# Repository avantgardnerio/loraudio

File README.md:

# open-oswst

Stealth LoRa radio mesh where the primary design principle is "only speak when spoken to".

## Hardware

- **Board**: [Heltec WiFi LoRa 32 V4](https://heltec.org/project/wifi-lora-32-v4/) (ESP32-S3 + SX1262, 863-928 MHz)
- **MCU**: ESP32-S3 rev 0.2, 16MB flash, 338 KiB RAM
- **Radio**: Semtech SX1262 LoRa transceiver, 915 MHz ISM band
- **Display**: SSD1306 128x64 OLED (I2C)

### Pin Map

| Function | GPIO |
|---|---|
| PRG button (PTT) | 0 (active LOW, internal pull-up) |
| White LED | 35 |
| Vext power enable | 36 (LOW = on) |
| OLED SDA | 17 |
| OLED SCL | 18 |
| OLED RST | 21 |
| LoRa SCK | 9 |
| LoRa MOSI | 10 |
| LoRa MISO | 11 |
| LoRa NSS | 8 |
| LoRa RST | 12 |
| LoRa DIO1 | 14 |
| LoRa BUSY | 13 |

## Dev Environment Setup

### Prerequisites

1. **Install Rust + Xtensa toolchain** via [espup](https://github.com/esp-rs/espup):

```bash
cargo install espup
espup install
```

2. **Create an ESP environment export script** (`~/export-esp.sh`):

```bash
export LIBCLANG_PATH="$HOME/.rustup/toolchains/esp/xtensa-esp32-elf-clang/esp-20.1.1_20250829/esp-clang/lib"
export PATH="$HOME/.rustup/toolchains/esp/xtensa-esp-elf/esp-15.2.0_20250920/xtensa-esp-elf/bin:$PATH"
```

The exact paths may vary — check `~/.rustup/toolchains/esp/` after `espup install`.

3. **Install flashing tools**:

```bash
cargo install espflash cargo-espflash ldproxy
```

4. **Optional**: install `picocom` for serial monitoring:

```bash
sudo apt install picocom
```

### Build

```bash
. ~/export-esp.sh
cargo build
```

ESP-IDF v5.5.x is downloaded automatically by `esp-idf-sys` on first build (takes a while).

### Flash

The firmware uses a custom partition table with a dedicated `open-oswst` NVS partition for device config. Since `espflash flash` overwrites the partition table with its own, you must re-write ours after flashing:

```bash
. ~/export-esp.sh

# 1. Flash firmware
espflash flash -p /dev/ttyACM0 target/xtensa-esp32s3-espidf/debug/open-oswst

# 2. Overwrite partition table with ours (espflash clobbers it in step 1)
espflash write-bin -p /dev/ttyACM0 0x8000 target/xtensa-esp32s3-espidf/debug/partition-table.bin

# 3. Write device config (only needed on first flash or to change config)
espflash write-bin -p /dev/ttyACM0 0xfad000 ~/phy/open-oswst_nvs.bin
```

Monitor separately:

```bash
picocom /dev/ttyACM0 -b 115200
```

### Device Config (NVS)

Device configuration lives in a dedicated `open-oswst` NVS partition at `0xfad000` (12KB), separate from the system NVS (PHY cal, WiFi, etc).

Generate a config image from `nvs_open-oswst.csv`:

```bash
# Generate NVS image (edit nvs_open-oswst.csv to change values)
python3 .embuild/espressif/python_env/idf5.5_py3.13_env/lib/python3.13/site-packages/esp_idf_nvs_partition_gen/nvs_partition_gen.py \
    generate nvs_open-oswst.csv ~/phy/open-oswst_nvs.bin 0x3000

# Flash to board
espflash write-bin -p /dev/ttyACM0 0xfad000 ~/phy/open-oswst_nvs.bin
```

Current config keys (namespace `config`):

| Key | Type | Values | Default |
|-----|------|--------|---------|
| `repeater` | u8 | 0=endpoint, 1=repeater | 0 |

There is also `nvs_config.py` for read-modify-write of the *system* NVS partition (preserving PHY cal data etc), but the dedicated partition approach above is preferred.

## Current Behavior

- Simplex push-to-talk voice radio over LoRa
- Hold **PRG button** (GPIO 0) to talk — audio is captured, Codec2-encoded at 1200 bps, and streamed as 4-frame LoRa packets (160ms audio each)
- Release to listen — received audio is decoded and played through I2S speaker (MAX98357A)
- OLED shows mode (RX Listening / TX Streaming / RX Audio) with RSSI and SNR on receive
- CSMA with preamble-aware jitter for collision avoidance
- Per-device config via dedicated NVS partition (repeater mode flag)
- **Next up**: repeater mesh relay

## Key Implementation Notes

- **Framework**: esp-idf-svc 0.52.1 (std Rust, not bare-metal)
- **Async**: `block_on` + `embassy_futures::select` for zero-polling PTT/RX racing
- **LoRa driver**: `lora-phy` (upstream git, 3.0.2-alpha) with `GenericSx126xInterfaceVariant`
- **GPIO type erasure**: `degrade_input()`/`degrade_output()` required for lora-phy's generic interface
- **SPI async**: `CONFIG_SPI_MASTER_ISR_IN_IRAM` disabled in `sdkconfig.defaults`
- **defmt workaround**: `defmt-discard.x` linker script discards defmt sections that break ESP-IDF flash layout
- **Stack**: 65536 bytes for main task (Codec2 init needs large stack temporaries)

## Project Structure

```
src/main.rs          # Entry point, channels, NVS config read
src/radio.rs         # SPI + LoRa init, IRQ-driven RX/TX loop, CSMA
src/app.rs           # PTT, ADC, OLED, Codec2, I2S speaker
partitions.csv       # Custom partition table (adds open-oswst NVS)
nvs_open-oswst.csv     # Default device config values
nvs_config.py        # Tool for read-modify-write of system NVS
sdkconfig.defaults   # ESP-IDF config overrides
defmt-discard.x      # Linker script to discard defmt sections
rust-toolchain.toml  # Pins to "esp" toolchain channel
build.rs             # Links defmt-discard.x
```

## Bill of Materials

### Handset (~$122)

| Component                                                                                       | Part                                                       | Qty | Est. Cost |
|-------------------------------------------------------------------------------------------------|------------------------------------------------------------|-----|-----------|
| [MCU + LoRa + GPS](https://www.amazon.com/dp/B0GCD9W6JZ?ref=ppx_yo2ov_dt_b_fed_asin_title&th=1) | Heltec WiFi LoRa 32 V4                                     | 1   | $42       |
| [RF amplifier](https://www.amazon.com/dp/B0DQBJVR91?ref=ppx_yo2ov_dt_b_fed_asin_title)          | AB-IOT-868 "Air Buddy" (902-928 MHz, bidirectional TX+LNA) | 1   | $26       |
| [Speaker amp](https://www.amazon.com/dp/B0DPJRLMDJ?ref=ppx_yo2ov_dt_b_fed_asin_title)           | MAX98357A I2S Class D breakout                             | 1   | $3        |
| [Speaker](https://www.amazon.com/dp/B0BTP67F81?ref=ppx_yo2ov_dt_b_fed_asin_title&th=1)          | 8 ohm 1W mini (JST-PH1.25mm)                               | 1   | $2.50     |
| [Microphone](https://www.amazon.com/dp/B0B7SP6GYX?ref=ppx_yo2ov_dt_b_fed_asin_title)            | MAX9814 electret with AGC (analog out)                     | 1   | $4        |
| [Antenna](https://www.amazon.com/dp/B0D47HVCK7?ref=ppx_yo2ov_dt_b_fed_asin_title&th=1)          | 5 dBi SMA whip (915 MHz)                                   | 1   | $6        |
| [Battery](https://www.amazon.com/dp/B0FPCWFFYB?ref=ppx_yo2ov_dt_b_fed_asin_title)               | YELUFT 1S 103450 3.7V 2000mAh LiPo (JST 1.25)              | 1   | $24       |
| [encoder](https://www.amazon.com/dp/B07F24TRYG?ref=ppx_yo2ov_dt_b_fed_asin_title)               | EC11 rotary encoder w/ push button (Taiss)                 | 2   | $1.25     |
| [Power switch](https://www.amazon.com/dp/B0DN69L9SG?ref=ppx_yo2ov_dt_b_fed_asin_title&th=1)     | SS12F15 mini slide switch (SPDT)                           | 1   | $0.30     |
| [PTT button](https://www.amazon.com/dp/B015X34IP6?ref=ppx_yo2ov_dt_b_fed_asin_title&th=1)       | Ulincos U16A1 16mm metal momentary, flush                  | 1   | $8        |
| [Speaker jack](https://www.amazon.com/dp/B01ASF0LW8?ref=ppx_yo2ov_dt_b_fed_asin_title)          | 2.5mm TRS chassis mount (Calrad 30-714 or similar)         | 1   | $0.66     |
| [Mic/PTT jack](https://www.amazon.com/dp/B00ZYWJ1DG?ref=ppx_yo2ov_dt_b_fed_asin_title)          | 3.5mm TRS chassis mount w/ switch (CESS)                   | 1   | $2        |
| [F2F SMA](https://www.amazon.com/dp/B0FB3R5WRL?ref=ppx_yo2ov_dt_b_fed_asin_title&th=1)          | Female to Female SMA                                       | 1 | $1        |

## License

TBD

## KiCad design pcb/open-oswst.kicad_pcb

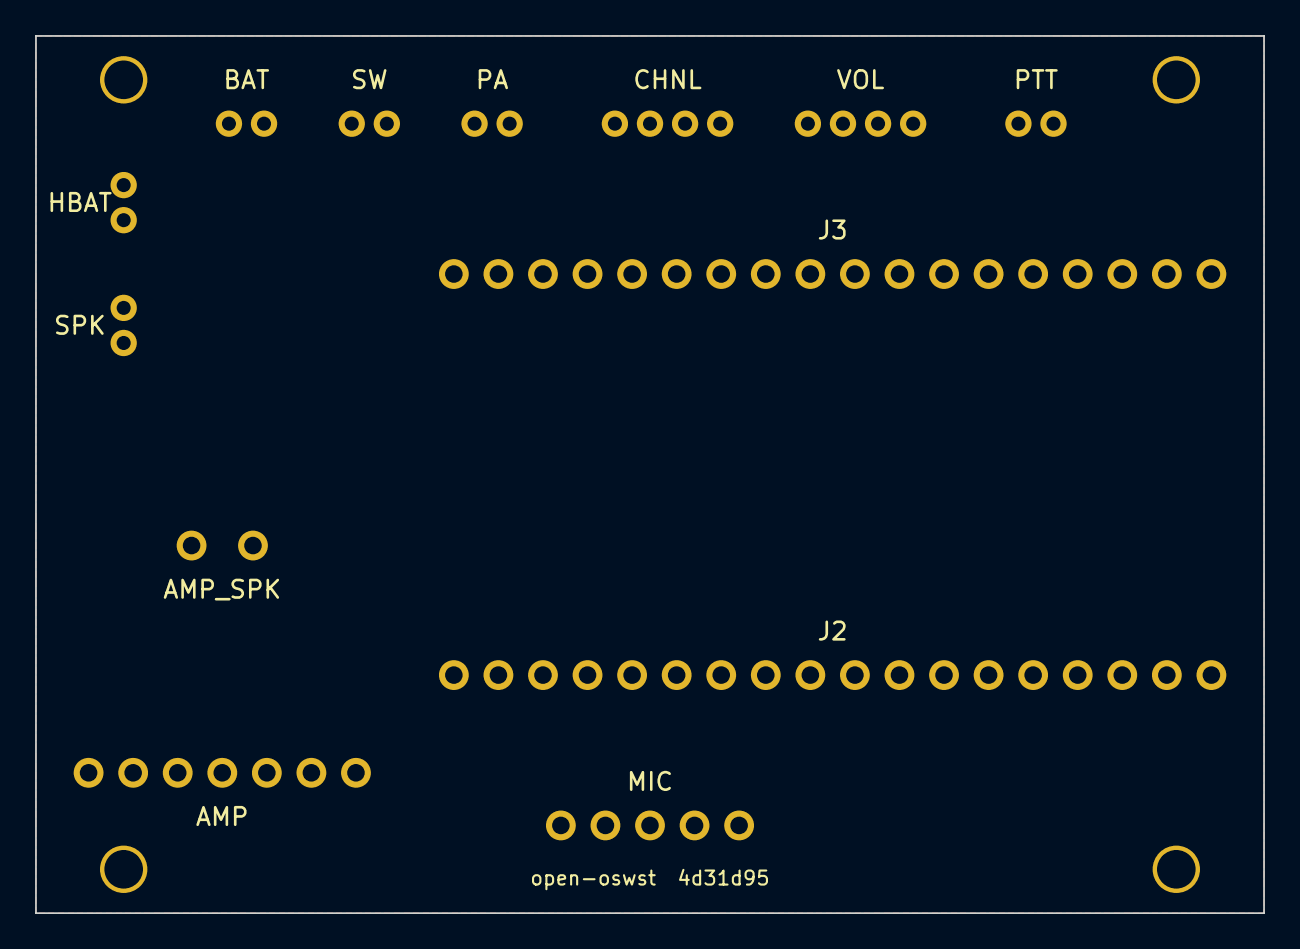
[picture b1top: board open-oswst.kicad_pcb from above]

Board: 2 copper layers, 70.0 x 50.0 mm, 17 parts (0 on the bottom side), 17 nets, no tracks yet.

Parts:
AMP: PinHeader_1x7_P2.54mm
AMP_SPK: PinHeader_1x2_P3.5mm
BAT: JST_PH_B2B
CHNL: JST_PH_B4B
H1, H2, H3, H4: MountingHole_2.2mm
HBAT: JST_PH_B2B
J2, J3: PinHeader_1x18_P2.54mm
MIC: PinHeader_1x5_P2.54mm
PA: JST_PH_B2B
PTT: JST_PH_B2B
SPK: JST_PH_B2B
SW: JST_PH_B2B
VOL: JST_PH_B4B

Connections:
BCLK: AMP.BCLK, J2.GPIO47
CHNL_A: CHNL.A, J3.GPIO7
CHNL_B: CHNL.B, J3.GPIO6
CHNL_SW: CHNL.SW, J3.GPIO5
DIN: AMP.DIN, J2.GPIO33
GND: AMP.GND, BAT.-, CHNL.GND, HBAT.-, J2.GND, J3.GND, MIC.GND, PA.-, PTT.2, VOL.GND
LRC: AMP.LRC, J2.GPIO48
MIC_OUT: J3.GPIO4, MIC.OUT
PTT: J2.GPIO0, PTT.1
SPK+: AMP_SPK.+, SPK.+
SPK-: AMP_SPK.-, SPK.-
VBAT: BAT.+, SW.1
VOL_A: J3.GPIO3, VOL.A
VOL_B: J3.GPIO2, VOL.B
VOL_SW: J3.GPIO1, VOL.SW
VSW: HBAT.+, PA.+, SW.2
Ve: AMP.Vin, J2.Ve_a, J2.Ve_b, MIC.VDD

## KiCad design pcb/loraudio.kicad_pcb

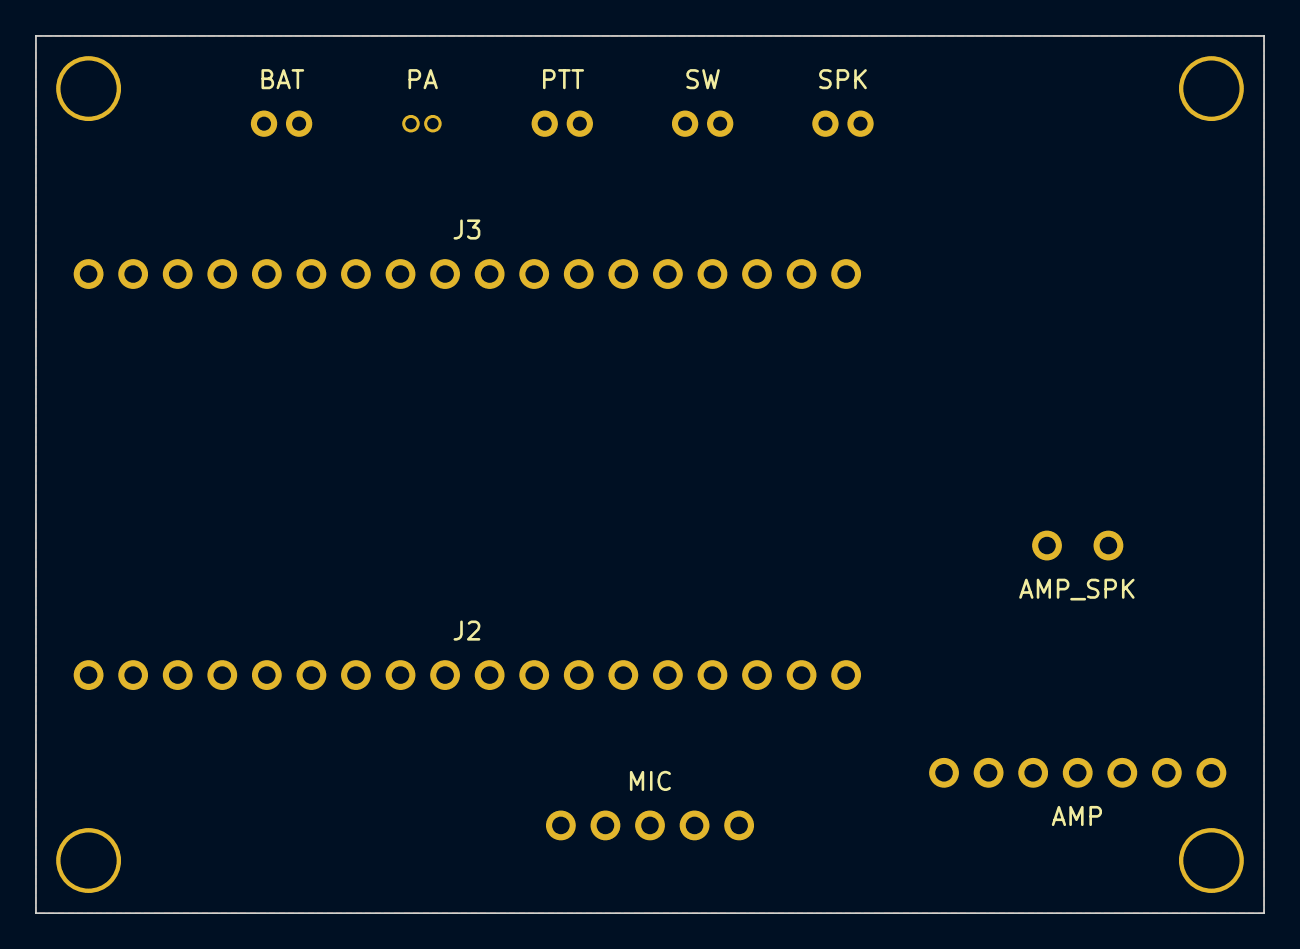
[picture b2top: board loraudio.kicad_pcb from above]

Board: 2 copper layers, 70.0 x 50.0 mm, 14 parts (0 on the bottom side), 11 nets, no tracks yet.

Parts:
AMP: PinHeader_1x7_P2.54mm
AMP_SPK: PinHeader_1x2_P3.5mm
BAT: JST_PH_B2B
H1, H2, H3, H4: MountingHole_3.2mm
J2, J3: PinHeader_1x18_P2.54mm
MIC: PinHeader_1x5_P2.54mm
PA: JST_SH_B2B
PTT: JST_PH_B2B
SPK: JST_PH_B2B
SW: JST_PH_B2B

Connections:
3V3: AMP.Vin, J3.3V3a, MIC.VDD
BCLK: AMP.BCLK, J3.GPIO3
DIN: AMP.DIN, J3.GPIO5
GND: AMP.GND, BAT.-, J2.GND, J3.GND, MIC.GND, PA.-, PTT.2
LRC: AMP.LRC, J3.GPIO4
MIC_OUT: J3.GPIO7, MIC.OUT
PTT: J2.GPIO0, PTT.1
SPK+: AMP_SPK.+, SPK.+
SPK-: AMP_SPK.-, SPK.-
VBAT: BAT.+, SW.1
VSW: J3.3V3b, PA.+, SW.2

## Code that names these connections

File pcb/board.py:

#!/usr/bin/env python3
"""Generate the open-oswst PCB."""

import subprocess
from kicad import Board

board = Board()
git_sha = subprocess.check_output(["git", "rev-parse", "--short", "HEAD"], text=True).strip()

# 70x50mm landscape, centered on A4 (297x210mm)
BX, BY = 113, 113  # board origin
BW, BH = 70, 50    # board size
INSET_LR = 5        # hole center distance from left/right edges
INSET_TB = 2.5      # hole center distance from top/bottom edges

board.add_rect(BX, BY, BW, BH)

for x in (BX + INSET_LR, BX + BW - INSET_LR):
    for y in (BY + INSET_TB, BY + BH - INSET_TB):
        board.add_mounting_hole(x, y, drill=2.2)

# Connectors along top edge — fit between drill holes (INSET_LR)
cx, cy = BX + INSET_LR + 7, BY + 5
board.add_jst_ph(cx, cy, pins=2, label="BAT",
                 pad_labels=["+", "-"], pad_nets=["VBAT", "GND"]); cx += 7
board.add_jst_ph(cx, cy, pins=2, label="SW",
                 pad_nets=["VBAT", "VSW"]); cx += 7
board.add_jst_ph(cx, cy, pins=2, label="PA",
                 pad_labels=["+", "-"], pad_nets=["VSW", "GND"]); cx += 10
board.add_jst_ph(cx, cy, pins=4, label="CHNL",
                 pad_labels=["A", "B", "SW", "GND"],
                 pad_nets=["CHNL_A", "CHNL_B", "CHNL_SW", "GND"]); cx += 11
board.add_jst_ph(cx, cy, pins=4, label="VOL",
                 pad_labels=["A", "B", "SW", "GND"],
                 pad_nets=["VOL_A", "VOL_B", "VOL_SW", "GND"]); cx += 10
board.add_jst_ph(cx, cy, pins=2, label="PTT",
                 pad_nets=["PTT", "GND"])

# HBAT: feeds VSW out to Heltec's onboard SH1.25-2P LiPo input via an M2M pigtail.
# Heltec's battery input accepts 3.3-4.2V (per datasheet 3.2), so raw LiPo is correct here.
# Placed above SPK so VSW from BAT/SW (top of board) doesn't cross the SPK+/SPK- traces.
board.add_jst_ph(BX + 5, BY + INSET_TB + 7, pins=2, label="HBAT", angle=90,
                 pad_labels=["+", "-"], pad_nets=["VSW", "GND"])

# SPK connector on left edge (rotated 90°, routes down to AMP_SPK)
board.add_jst_ph(BX + 5, BY + INSET_TB + 14, pins=2, label="SPK", angle=90,
                 pad_labels=["-", "+"], pad_nets=["SPK-", "SPK+"])

# Heltec V4 headers — two 18-pin rows
J3_SPAN = 17 * 2.54  # 18 pins, 17 gaps
HELTEC_WIDTH = 22.86  # distance between J3 and J2 header rows
HY = BY + BH / 2 - HELTEC_WIDTH / 2  # J3 y (top row)

board.add_header(BX + BW - 3 - J3_SPAN / 2, HY, pins=18, label="J3",
                 pad_labels=["GPIO7", "GPIO6", "GPIO5", "GPIO4", "GPIO3", "GPIO2",
                             "GPIO1", "GPIO38", "GPIO39", "GPIO40", "GPIO41", "GPIO42",
                             "GPIO45", "GPIO46", "GPIO37", "3V3a", "3V3b", "GND"],
                 pad_nets=["CHNL_A", "CHNL_B", "CHNL_SW", "MIC_OUT", "VOL_A", "VOL_B",
                           "VOL_SW", None, None, None, None, None,
                           None, None, None, None, None, "GND"])

# Heltec V4 J2 header (right side, pin 18→1 top to bottom)
J2_SPAN = J3_SPAN  # same 18 pins
board.add_header(BX + BW - 3 - J2_SPAN / 2, HY + HELTEC_WIDTH, pins=18, label="J2",
                 pad_labels=["GPIO19", "GPIO20", "GPIO21", "GPIO26", "GPIO48", "GPIO47",
                             "GPIO33", "GPIO34", "GPIO35", "GPIO36", "GPIO0", "RST",
                             "GPIO43", "GPIO44", "Ve_b", "Ve_a", "5V", "GND"],
                 pad_nets=[None, None, None, None, "LRC", "BCLK",
                           "DIN", None, None, None, "PTT", None,
                           None, None, "Ve", "Ve", None, "GND"])

# Board headers along bottom edge
board.add_header(BX + BW / 2, BY + BH - 5, pins=5, label="MIC",
                 pad_labels=["AR", "OUT", "GAIN", "VDD", "GND"],
                 pad_nets=[None, "MIC_OUT", None, "Ve", "GND"])
AMP_X = BX + 3 + 3 * 2.54
AMP_Y = BY + BH - 3 - 5
board.add_header(AMP_X, AMP_Y, pins=7, label="AMP", angle=180,
                 pad_labels=["Vin", "GND", "SD", "GAIN", "DIN", "BCLK", "LRC"],
                 pad_nets=["Ve", "GND", None, None, "DIN", "BCLK", "LRC"])
board.add_header(AMP_X, AMP_Y - 12.954, pins=2, label="AMP_SPK", angle=180,
                 pitch=3.5, pad_labels=["+", "-"], pad_nets=["SPK+", "SPK-"])

# Silkscreen — project name and git SHA
board.add_text(BX + BW / 2, BY + BH - 2, f"open-oswst  {git_sha}", size=0.8, thickness=0.12)

# Ground plane — GND zone covering full board, both copper layers
board.add_zone("GND", [
    (BX, BY), (BX + BW, BY), (BX + BW, BY + BH), (BX, BY + BH),
], clearance=0.25, thermal_gap=0.3, thermal_bridge_width=0.3)

board.save("open-oswst.kicad_pcb")

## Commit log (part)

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2026-04-24 docs
2026-04-25 oversight
2026-04-25 monitor script
2026-04-25 Remove calculated air time
2026-04-27 [WIP] speaker refactor
2026-04-28 [WIP] add case model
2026-04-28 [WIP] delete
2026-05-04 [WIP] geometry fixes
2026-05-05 fix USB
2026-05-05 taper lanyard
2026-05-06 speaker test
2026-05-06 mic test
2026-05-08 generate kicad
2026-05-08 no perfboard
2026-05-08 Add a groundplane
2026-05-08 ground plane
2026-05-11 fix pinout
2026-05-27 don't lose doc
2026-05-28 oriented correctly
2026-05-28 correct side of board
2026-05-28 move spkr
2026-05-28 good rev
2026-06-05 rev5 :(
